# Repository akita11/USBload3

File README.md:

# USBload3

モバイルバッテリをマイコンボード等で給電するときに、電源が切れてしまう現象を回避するためのものです。定期的に負荷をかける（少し電流を流す）ことで、電源が切れることを回避します。流す電流量と電流を流す周期は設定できます。[USBload](https://github.com/akita11/USBload)と機能は同一で、受電側のUSBコネクタのみ異なります。

## 使い方

- 本機のUSB Aコネクタとマイコンボード等を、市販のUSBケーブルで接続する
- 本機のUSB TypeCコネクタとモバイルバッテリを、市販のUSBケーブルで接続する

モバイルバッテリを接続すると動作がはじまります。負荷がかかっている（電流が流れている）ときには本体LEDが点灯します。

## 設定の変更

[USBload](https://github.com/akita11/USBload)の資料を参照してください。なお負荷時のLEDは、LED横の「LED」と書いてあるパターン（半田ジャンパ）をカットすることでOFFにできます。

## Author

Junichi Akita (@akita11) / akita@ifdl.jp

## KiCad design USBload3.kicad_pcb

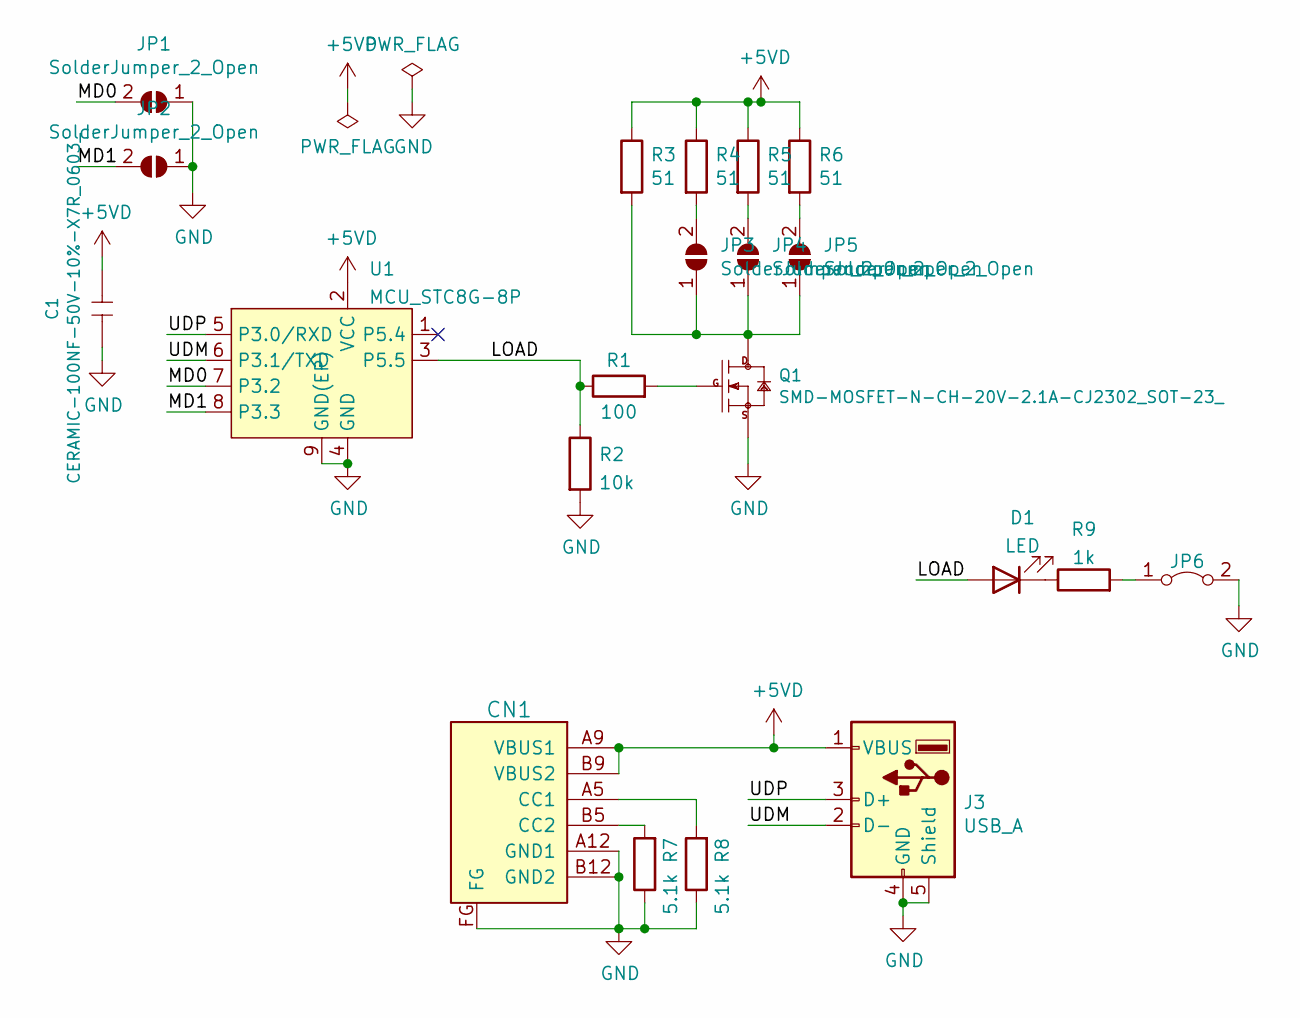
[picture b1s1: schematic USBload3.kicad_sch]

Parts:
C1: CERAMIC-100NF-50V-10%-X7R_0603_; C_0603_1608Metric; MPN CC0603KRX7R9BB104
CN1: CON_USB-C-6; USB-C_6P
D1: LED; LED_0603_1608Metric
J3: USB_A; USB_A_Stewart_SS-52100-001_Horizontal
JP1, JP2, JP3, JP4, JP5: SolderJumper_2_Open; SolderJumper-2_P1.3mm_Open_RoundedPad1.0x1.5mm
JP6: Jumper_2_Bridged; SolderJumper-2_P1.3mm_Bridged_Pad1.0x1.5mm
Q1: SMD-MOSFET-N-CH-20V-2.1A-CJ2302_SOT-23_; SOT-23; MPN CJ2302
R1: 100; R_0603_1608Metric
R2: 10k; R_0603_1608Metric
R3, R4, R5, R6: 51; R_0805_2012Metric
R7, R8: 5.1k; R_0603_1608Metric
R9: 1k; R_0603_1608Metric
U1: MCU_STC8G-8P; DFN-8-1EP_3x3mm_P0.5mm_EP1.66x2.38mm

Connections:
+5VD: C1.2, CN1.A9 (VBUS1), CN1.B9 (VBUS2), J3.1 (VBUS), R3.1, R4.1, R5.1, R6.1, U1.2 (VCC)
/LOAD: D1.2 (A), R1.1, R2.1, U1.3 (P5.5)
/MD0: JP1.2 (B), U1.7 (P3.2)
/MD1: JP2.2 (B), U1.8 (P3.3)
/UDM: J3.2 (D-), U1.6 (P3.1/TXD)
/UDP: J3.3 (D+), U1.5 (P3.0/RXD)
GND: C1.1, CN1.A12 (GND1), CN1.B12 (GND2), CN1.FG, J3.4 (GND), J3.5 (Shield), JP1.1 (A), JP2.1 (A), JP6.2 (B), Q1.2 (S), R2.2, R7.1, R8.1, U1.4 (GND), U1.9 (GND(EP))
unnamed: CN1.A5 (CC1), R8.2
unnamed: CN1.B5 (CC2), R7.2
unnamed: D1.1 (K), R9.1
unnamed: JP3.1 (A), JP4.1 (A), JP5.1 (A), Q1.3 (D), R3.2
unnamed: JP3.2 (B), R4.2
unnamed: JP4.2 (B), R5.2
unnamed: JP5.2 (B), R6.2
unnamed: JP6.1 (A), R9.2
unnamed: Q1.1 (G), R1.2

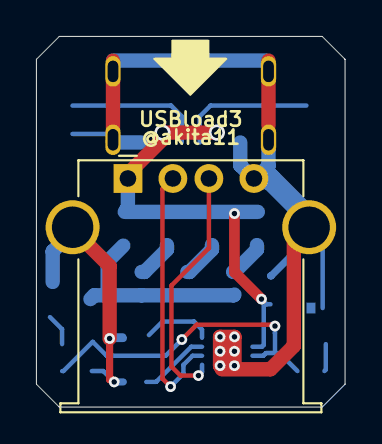
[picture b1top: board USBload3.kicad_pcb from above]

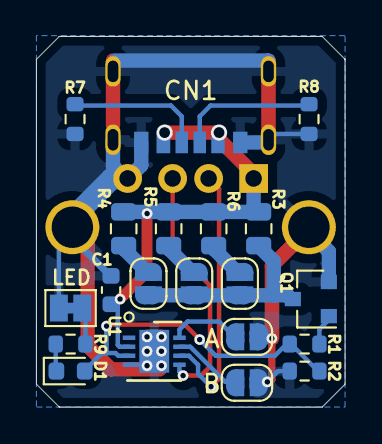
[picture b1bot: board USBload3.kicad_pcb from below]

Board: 2 copper layers, 17.1 x 20.6 mm, 21 parts (20 on the bottom side), 16 nets.
